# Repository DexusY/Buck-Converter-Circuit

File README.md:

# Step-Down Converter Based on Texas Instruments LMQ61460

This project is inspired by the typical application schematic from the Texas Instruments LMQ61460 datasheet. It implements a high-efficiency step-down (buck) converter, suitable for applications requiring stable voltage regulation.

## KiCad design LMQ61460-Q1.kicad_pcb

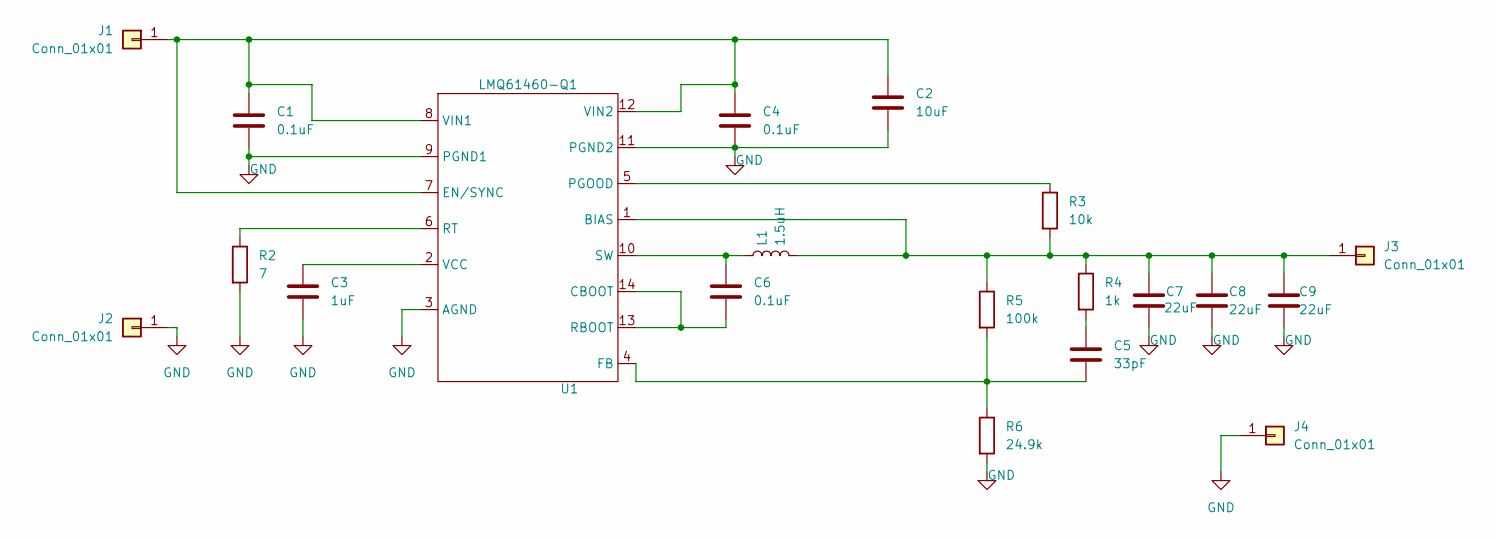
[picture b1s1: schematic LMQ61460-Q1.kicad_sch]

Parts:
C1: 0.1uF; C_0504_1310Metric
C2: 10uF; C_1206_3216Metric_Pad1.33x1.80mm_HandSolder
C3: 1uF; C_0402_1005Metric
C4, C6: 0.1uF; C_0402_1005Metric
C5: 33pF; C_0402_1005Metric
C7, C8, C9: 22uF; C_0805_2012Metric
J1, J2, J3, J4: Conn_01x01; Banana_Jack_1Pin
L1: 1.5uH; L_Coilcraft_XxL4020
R2: 7; R_0402_1005Metric
R3: 10k; R_0402_1005Metric
R4: 1k; R_0402_1005Metric
R5: 100k; R_0402_1005Metric
R6: 24.9k; R_0402_1005Metric
U1: LMQ61460-Q1

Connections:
GND: C1.2, C2.2, C3.2, C4.2, C7.2, C8.2, C9.2, J2.1, J4.1, R2.2, R6.2, U1.3 (AGND), U1.9 (PGND1), U1.11 (PGND2)
unnamed: C5.1, R4.2
unnamed: C1.1, C2.1, C4.1, J1.1, U1.7 (EN/SYNC), U1.8 (VIN1), U1.12 (VIN2)
unnamed: C7.1, C8.1, C9.1, J3.1, L1.2, R3.2, R4.1, R5.1, U1.1 (BIAS)
unnamed: C6.2, U1.13 (RBOOT), U1.14 (CBOOT)
unnamed: C5.2, R5.2, R6.1, U1.4 (FB)
unnamed: R3.1, U1.5 (PGOOD)
unnamed: R2.1, U1.6 (RT)
unnamed: C6.1, L1.1, U1.10 (SW)
unnamed: C3.1, U1.2 (VCC)

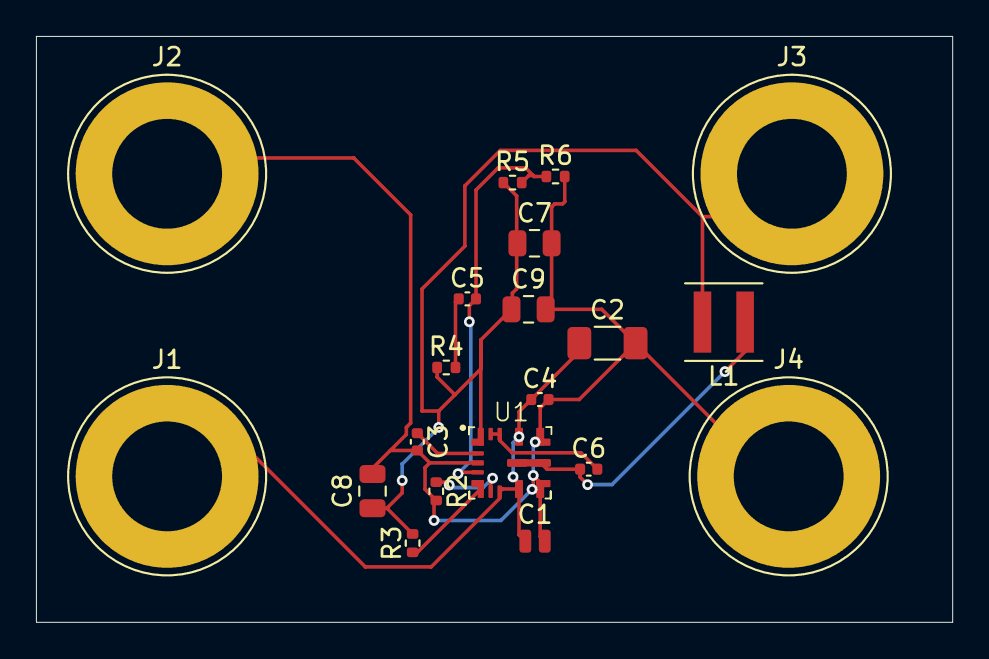
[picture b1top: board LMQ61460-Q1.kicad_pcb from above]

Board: 2 copper layers, 50.9 x 32.6 mm, 20 parts (0 on the bottom side), 10 nets.

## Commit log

2025-04-02 README.md
